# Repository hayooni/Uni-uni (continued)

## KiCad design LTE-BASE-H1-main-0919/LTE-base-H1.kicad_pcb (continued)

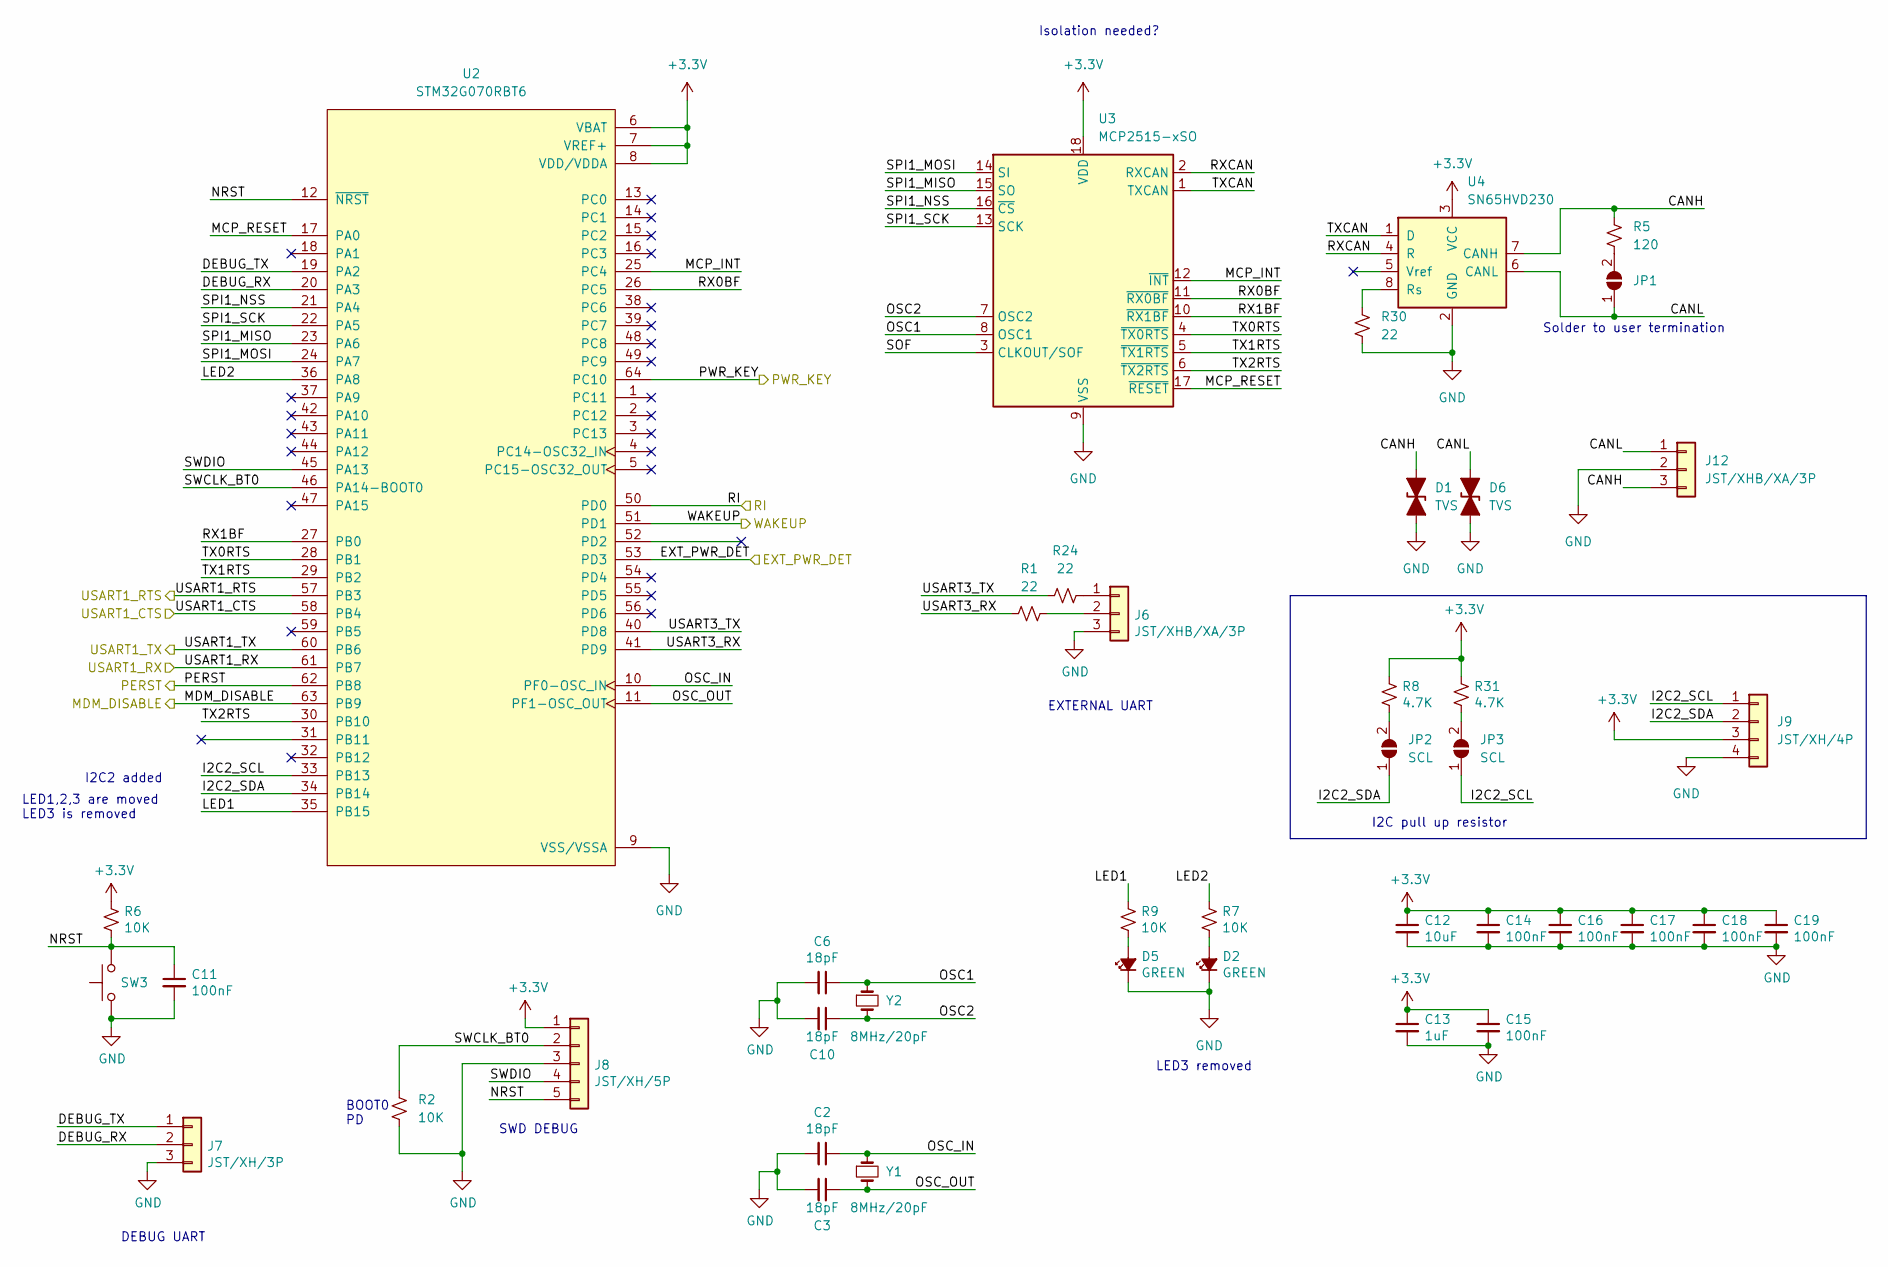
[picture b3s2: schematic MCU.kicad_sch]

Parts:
C2, C3, C6, C10: 18pF; C_0603_1608Metric; LCSC C1647
C11, C14, C15, C16, C17, C18, C19: 100nF; C_0603_1608Metric; LCSC C14663
C12: 10uF; C_0603_1608Metric; LCSC C19702
C13: 1uF; C_0603_1608Metric; LCSC C15849
D1, D6: TVS; D_SOD-323; LCSC C314256
D2, D5: GREEN; LED_0603_1608Metric; LCSC C72043
J6, J12: JST/XHB/XA/3P; JST_XA_S03B-XASK-1N-BN_1x03_P2.50mm_Horizontal; LCSC C95477
J7: JST/XH/3P; JST_XH_B3B-XH-A_1x03_P2.50mm_Vertical; LCSC C144394
J8: JST/XH/5P; JST_XH_B5B-XH-A_1x05_P2.50mm_Vertical; LCSC C157991
J9: JST/XH/4P; JST_XH_B4B-XH-A_1x04_P2.50mm_Vertical
JP1: SolderJumper_2_Open; SolderJumper-2_P1.3mm_Open_RoundedPad1.0x1.5mm
JP2, JP3: SCL; SolderJumper-2_P1.3mm_Open_RoundedPad1.0x1.5mm
R1, R24, R30: 22; R_0603_1608Metric; LCSC C23345
R2, R6, R7, R9: 10K; R_0603_1608Metric; LCSC C25804
R5: 120; R_0603_1608Metric; LCSC C22787
R8, R31: 4.7K; R_0603_1608Metric
SW3: SW_Push; SW_SPST_PTS645; LCSC C2834943
U2: STM32G070RBT6; LQFP-64_10x10mm_P0.5mm; LCSC C529340
U3: MCP2515-xSO; SOIC-18W_7.5x11.6mm_P1.27mm; LCSC C153782
U4: SN65HVD230; SOIC-8_3.9x4.9mm_P1.27mm
Y1, Y2: 8MHz/20pF; Crystal_SMD_5032-2Pin_5.0x3.2mm; LCSC C115962

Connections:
/BG96/DTR: U2.51 (PD1); also elsewhere on the board
/BG96/PWRKEY: U2.64 (PC10); also elsewhere on the board
/BG96/RI: U2.50 (PD0); also elsewhere on the board
/BG96/nPERST: U2.62 (PB8); also elsewhere on the board
/BG96/nW_DISABLE: U2.63 (PB9); also elsewhere on the board
/EXT_PWR_DET: U2.53 (PD3); also elsewhere on the board
/MCU/CANH: D1.2 (A2), J12.3, R5.1, U4.7 (CANH)
/MCU/CANL: D6.2 (A2), J12.1, JP1.1 (A), U4.6 (CANL)
/MCU/DEBUG_RX: J7.2, U2.20 (PA3)
/MCU/DEBUG_TX: J7.1, U2.19 (PA2)
/MCU/I2C2_SCL: J9.1, JP3.1 (A), U2.33 (PB13)
/MCU/I2C2_SDA: J9.2, JP2.1 (A), U2.34 (PB14)
/MCU/LED1: R9.1, U2.35 (PB15)
/MCU/LED2: R7.1, U2.36 (PA8)
/MCU/MCP_INT: U2.25 (PC4), U3.12 (~INT)
/MCU/MCP_RESET: U2.17 (PA0), U3.17 (~RESET)
/MCU/NRST: C11.1, J8.5, R6.2, SW3.1, U2.12 (~NRST)
/MCU/OSC1: C6.1, U3.8 (OSC1), Y2.1
/MCU/OSC2: C10.1, U3.7 (OSC2), Y2.2
/MCU/OSC_IN: C2.1, U2.10 (PF0-OSC_IN), Y1.1
/MCU/OSC_OUT: C3.1, U2.11 (PF1-OSC_OUT), Y1.2
/MCU/RX0BF: U2.26 (PC5), U3.11 (~RX0BF)
/MCU/RX1BF: U2.27 (PB0), U3.10 (~RX1BF)
/MCU/RXCAN: U3.2 (RXCAN), U4.4 (R)
/MCU/SOF: U3.3 (CLKOUT/SOF)
/MCU/SPI1_MISO: U2.23 (PA6), U3.15 (SO)
/MCU/SPI1_MOSI: U2.24 (PA7), U3.14 (SI)
/MCU/SPI1_NSS: U2.21 (PA4), U3.16 (~CS)
/MCU/SPI1_SCK: U2.22 (PA5), U3.13 (SCK)
/MCU/SWCLK_BT0: J8.2, R2.1, U2.46 (PA14-BOOT0)
/MCU/SWDIO: J8.4, U2.45 (PA13)
/MCU/TX0RTS: U2.28 (PB1), U3.4 (~TX0RTS)
/MCU/TX1RTS: U2.29 (PB2), U3.5 (~TX1RTS)
/MCU/TX2RTS: U2.30 (PB10), U3.6 (~TX2RTS)
/MCU/TXCAN: U3.1 (TXCAN), U4.1 (D)
/MCU/USART1_CTS: U2.58 (PB4); also elsewhere on the board
/MCU/USART1_RTS: U2.57 (PB3); also elsewhere on the board
/MCU/USART1_RX: U2.61 (PB7); also elsewhere on the board
/MCU/USART1_TX: U2.60 (PB6); also elsewhere on the board
/MCU/USART3_RX: R1.1, U2.41 (PD9)
/MCU/USART3_TX: R24.1, U2.40 (PD8)
GND: C2.2, C3.2, C6.2, C10.2, C11.2, C12.2, C13.2, C14.2, C15.2, C16.2, C17.2, C18.2, C19.2, D1.1 (A1), D2.1 (K), D5.1 (K), D6.1 (A1), J6.3, J7.3, J8.3, J9.4, J12.2, R2.2, R30.1, SW3.2, U2.9 (VSS/VSSA), U3.9 (VSS), U4.2 (GND); also elsewhere on the board
unnamed: D2.2 (A), R7.2
unnamed: D5.2 (A), R9.2
unnamed: J6.1, R24.2
unnamed: J6.2, R1.2
unnamed: JP1.2 (B), R5.2
unnamed: JP2.2 (B), R8.2
unnamed: JP3.2 (B), R31.2
unnamed: R30.2, U4.8 (Rs)

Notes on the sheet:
LED1,2,3 are moved LED3 is removed
LED3 removed
BOOT0 PD
SWD DEBUG
I2C pull up resistor
Isolation needed?
I2C2 added
Solder to user termination
EXTERNAL UART
DEBUG UART

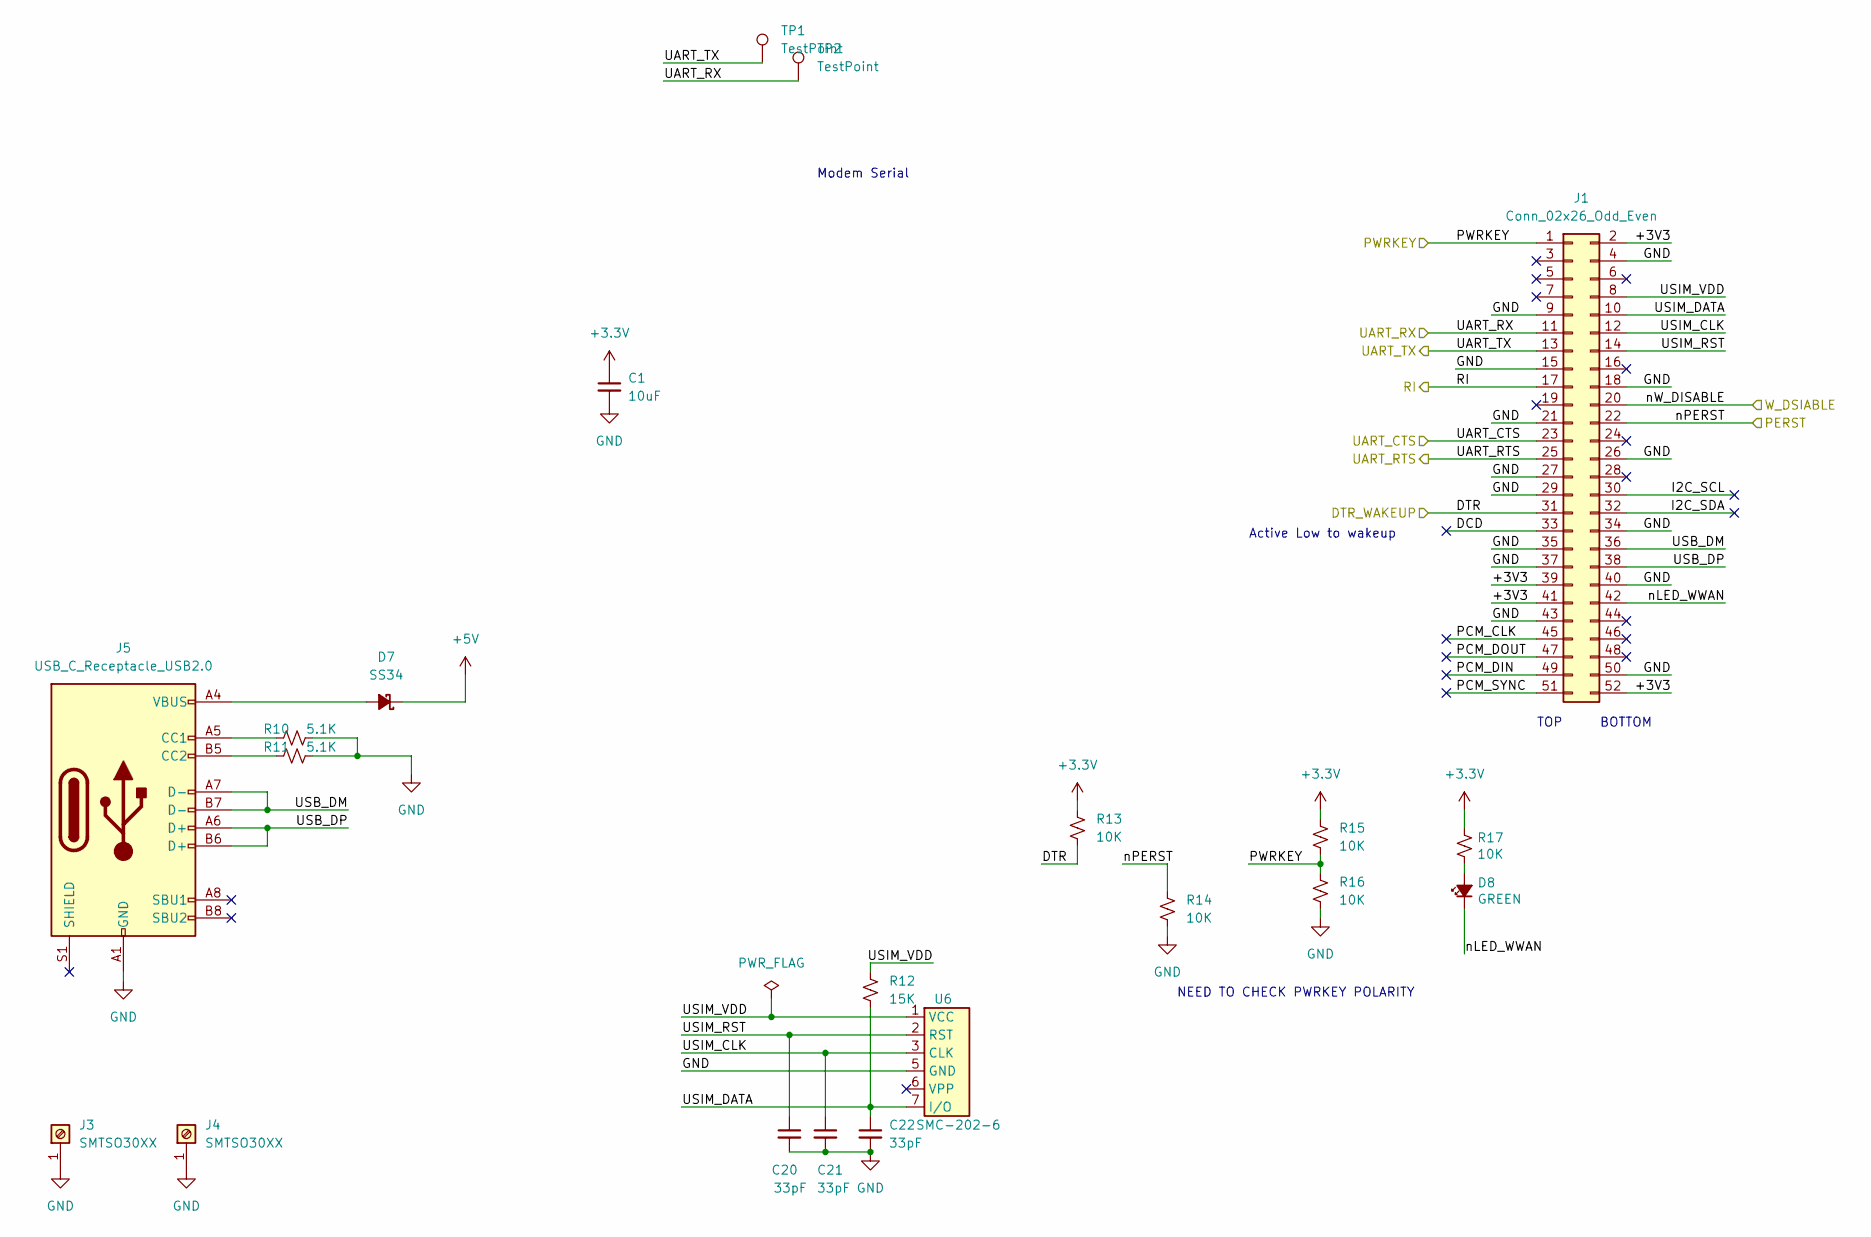
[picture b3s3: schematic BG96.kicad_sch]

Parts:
C1: 10uF; C_0603_1608Metric; LCSC C19702
C20, C21, C22: 33pF; C_0603_1608Metric_Pad1.08x0.95mm_HandSolder; LCSC C1663
D7: SS34; D_SMA; LCSC C8678
D8: GREEN; LED_0603_1608Metric; LCSC C72043
J1: Conn_02x26_Odd_Even; BUS_PCI_Express_Mini_Full; LCSC C444928
J3, J4: SMTSO30XX
J5: USB_C_Receptacle_USB2.0; USB_C_Receptacle_HRO_TYPE-C-31-M-12; LCSC C165948
R10, R11: 5.1K; R_0805_2012Metric; LCSC C27834
R12: 15K; R_0603_1608Metric_Pad0.98x0.95mm_HandSolder; LCSC C22809
R13, R14, R15, R16: 10K; R_0603_1608Metric_Pad0.98x0.95mm_HandSolder; LCSC C25804
R17: 10K; R_0603_1608Metric; LCSC C25804
TP1, TP2: TestPoint; TestPoint_Keystone_5000-5004_Miniature
U6: SMC-202-6; LCSC C266634

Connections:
+5V: D7.1 (K); also elsewhere on the board
/BG96/DCD: J1.33
/BG96/DTR: J1.31, R13.2; also elsewhere on the board
/BG96/I2C_SCL: J1.30
/BG96/I2C_SDA: J1.32
/BG96/PCM_CLK: J1.45
/BG96/PCM_DIN: J1.49
/BG96/PCM_DOUT: J1.47
/BG96/PCM_SYNC: J1.51
/BG96/PWRKEY: J1.1, R15.2, R16.1; also elsewhere on the board
/BG96/RI: J1.17; also elsewhere on the board
/BG96/UART_CTS: J1.23; also elsewhere on the board
/BG96/UART_RTS: J1.25; also elsewhere on the board
/BG96/UART_RX: J1.11, TP2.1; also elsewhere on the board
/BG96/UART_TX: J1.13, TP1.1; also elsewhere on the board
/BG96/USB_DM: J1.36, J5.A7 (D-), J5.B7 (D-)
/BG96/USB_DP: J1.38, J5.A6 (D+), J5.B6 (D+)
/BG96/USIM_CLK: C21.1, J1.12, U6.3 (CLK)
/BG96/USIM_DATA: C22.1, J1.10, R12.2, U6.7 (I/O)
/BG96/USIM_RST: C20.1, J1.14, U6.2 (RST)
/BG96/USIM_VDD: J1.8, R12.1, U6.1 (VCC)
/BG96/nLED_WWAN: D8.1 (K), J1.42
/BG96/nPERST: J1.22, R14.1; also elsewhere on the board
/BG96/nW_DISABLE: J1.20; also elsewhere on the board
GND: C1.2, C20.2, C21.2, C22.2, J1.4, J1.9, J1.15, J1.18, J1.21, J1.26, J1.27, J1.29, J1.34, J1.35, J1.37, J1.40, J1.43, J1.50, J3.1, J4.1, J5.A1 (GND), J5.A12 (GND), J5.B1 (GND), J5.B12 (GND), R10.1, R11.1, R14.2, R16.2, U6.5 (GND); also elsewhere on the board
unnamed: D7.2 (A), J5.A4 (VBUS), J5.A9 (VBUS), J5.B4 (VBUS), J5.B9 (VBUS)
unnamed: D8.2 (A), R17.2
unnamed: J5.A5 (CC1), R10.2
unnamed: J5.B5 (CC2), R11.2

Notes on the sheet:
Modem Serial
BOTTOM
Active Low to wakeup
TOP
NEED TO CHECK PWRKEY POLARITY

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
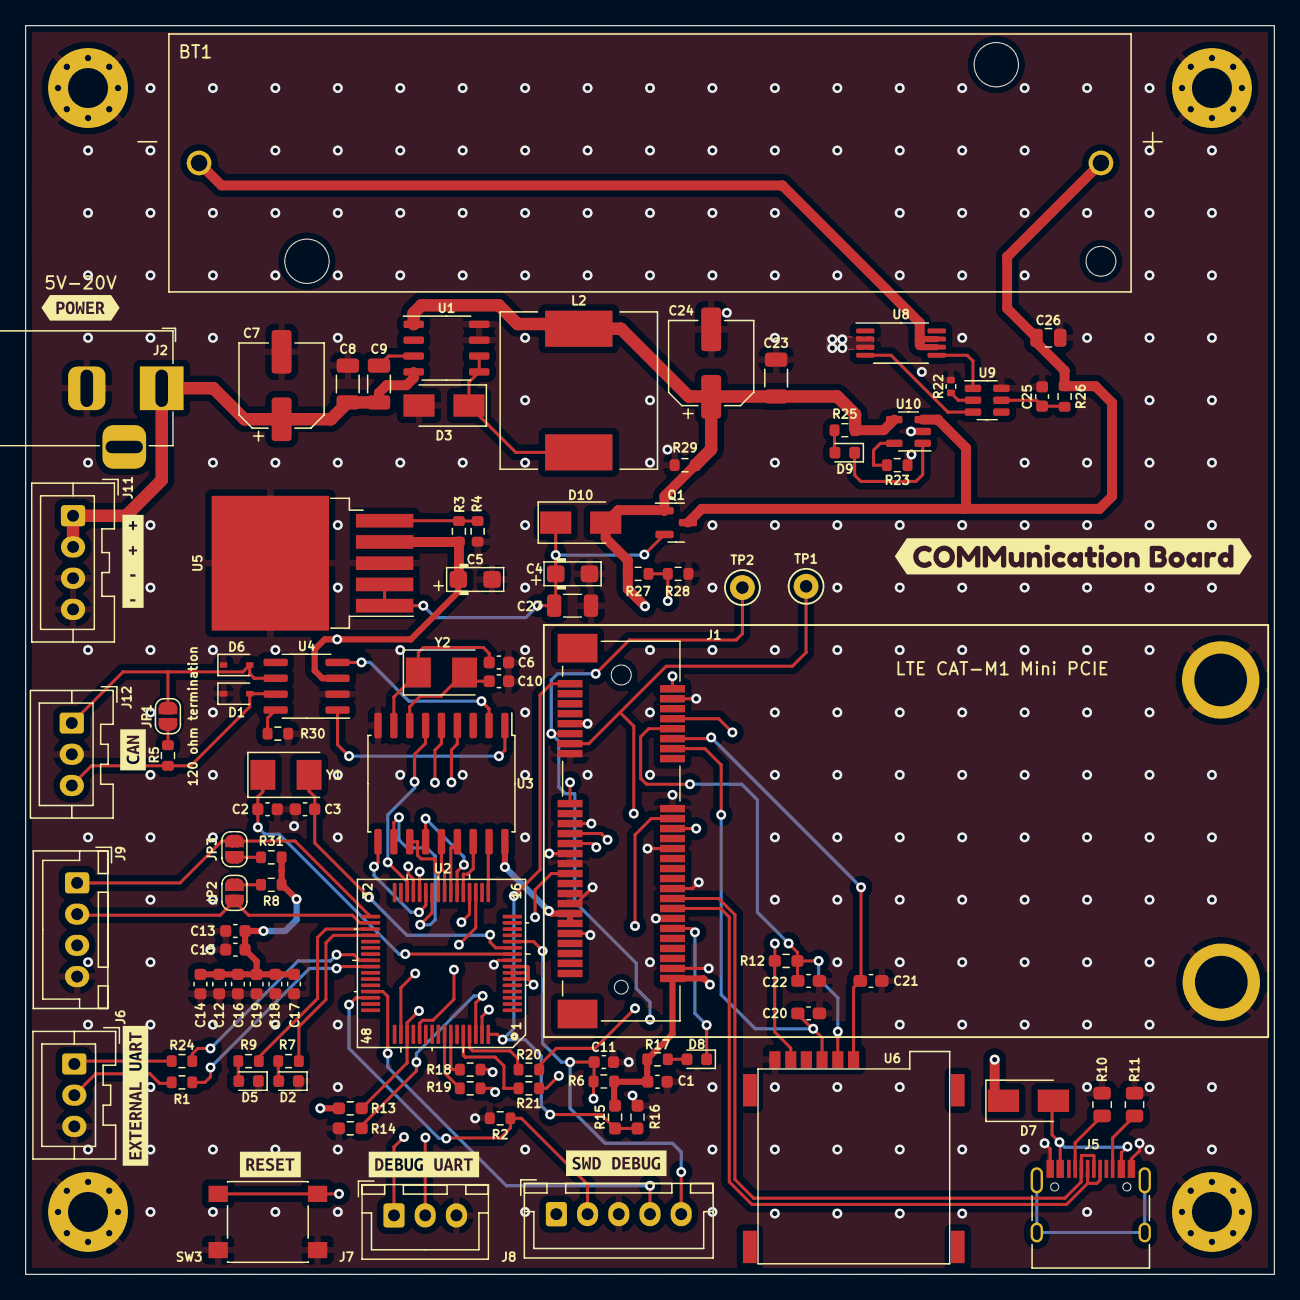
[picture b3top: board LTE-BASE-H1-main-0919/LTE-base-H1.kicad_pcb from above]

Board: 4 copper layers, 100.0 x 100.0 mm, 110 parts (0 on the bottom side), 80 nets.

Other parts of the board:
kibuzzard-61FFCA2F: G***; kibuzzard-61FFCA2F
kibuzzard-61FFCA5B: G***; kibuzzard-61FFCA5B
kibuzzard-61FFCA89: G***; kibuzzard-61FFCA89
kibuzzard-61FFCAE2: G***; kibuzzard-61FFCAE2
kibuzzard-61FFCAF5: G***; kibuzzard-61FFCAF5
kibuzzard-61FFCBAB: G***; kibuzzard-61FFCBAB
kibuzzard-61FFCBC3: G***; kibuzzard-61FFCBC3
kibuzzard-6200D0E6: G***; kibuzzard-6200D0E6

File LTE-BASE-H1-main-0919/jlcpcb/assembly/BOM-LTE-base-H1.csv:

Comment,Designator,Footprint,LCSC
DMG2307L,Q1,SOT-23,C102620
8MHz/20pF,"Y1,Y2",Crystal_SMD_5032-2Pin_5.0x3.2mm,C115962
1K,R22,R_0402_1005Metric,C11702
SN65HVD230,U4,SOIC-8_3.9x4.9mm_P1.27mm,C12084
Barrel Jack,J2,BarrelJack_Horizontal,C136744
DW01A,U9,SOT-23-6,C14213
JST/XHB/XA/3P,"J12,J6,J7",JST_XA_B03B-XASK-1_1x03_P2.50mm_Vertical,C144394
JST/XHB/XA/4P,"J11,J9",JST_XA_B04B-XASK-1_1x04_P2.50mm_Vertical,C144395
100nF,"C11,C14,C15,C16,C17,C18,C19,C25",C_0603_1608Metric,C14663
MCP73831-2-OT,U10,SOT-23-5,C14879
MCP2515-xSO,U3,SOIC-18W_7.5x11.6mm_P1.27mm,C153782
JST/XH/5P,J8,JST_XH_B5B-XH-A_1x05_P2.50mm_Vertical,C157991
1uF,C13,C_0603_1608Metric,C15849
FS8205A,U8,TSSOP-8_4.4x3mm_P0.65mm,C16052
18pF,"C10,C2,C3,C6",C_0603_1608Metric,C1647
USB_C_Receptacle_USB2.0,J5,USB_C_Receptacle_HRO_TYPE-C-31-M-12,C165948
33pF,"C20,C21,C22",C_0603_1608Metric_Pad1.08x0.95mm_HandSolder,C1663
4.7uF,C26,C_0805_2012Metric,C1779
1uF,"C23,C27,C8,C9",C_1206_3216Metric,C1848
10uF,"C1,C12",C_0603_1608Metric,C19702
1K,R25,R_0603_1608Metric,C21190
100,R26,R_0603_1608Metric,C22775
120,R5,R_0603_1608Metric,C22787
15K,R12,R_0603_1608Metric_Pad0.98x0.95mm_HandSolder,C22809
10.69K,R3,R_0603_1608Metric,C22857
RED,D9,LED_0603_1608Metric,C2286
2K,R23,R_0603_1608Metric,C22975
4.7K,"R31,R8",R_0603_1608Metric,C23162
22,"R1,R18,R19,R20,R21,R24,R30",R_0603_1608Metric,C23345
10K,"R13,R14,R15,R16,R17,R2,R27,R29,R4,R6,R7,R9",R_0603_1608Metric_Pad0.98x0.95mm_HandSolder,C25804
SMC-202-6,U6,SMC-202-6,C266634
5.1K,"R10,R11",R_0805_2012Metric,C27834
SW_Push,SW3,SW_SPST_PTS645,C2834943
TVS,"D1,D6",D_SOD-323,C314256
20K,R28,R_0603_1608Metric,C4184
Conn_02x26_Odd_Even,J1,BUS_PCI_Express_Mini_Full,C444928
47uF,"C24,C7",CP_Elec_6.3x5.8,C445227
STM32G070RBT6,U2,LQFP-64_10x10mm_P0.5mm,C529340
10uF,"C4,C5",CP_EIA-3216-18_Kemet-A,C7171
GREEN,"D2,D5,D8",LED_0603_1608Metric,C72043
XL2012,U1,SOP-8_3.9x4.9mm_P1.27mm,C73338
SS34,"D10,D3,D7",D_SMA,C8678
MIC29302WU,U5,TO-263-5_TabPin3,C9013
47uH/3A,L2,L_12x12mm_H8mm,C9906
MountingHole_Pad,H4,MountingHole_3.2mm_M3_Pad_Via,
SMTSO30XX,J4,SMTSO30XX,
MountingHole_Pad,H2,MountingHole_3.2mm_M3_Pad_Via,
SMTSO30XX,J3,SMTSO30XX,
MountingHole_Pad,H1,MountingHole_3.2mm_M3_Pad_Via,
SolderJumper_2_Open,JP1,SolderJumper-2_P1.3mm_Open_RoundedPad1.0x1.5mm,
MountingHole_Pad,H3,MountingHole_3.2mm_M3_Pad_Via,
TestPoint,TP2,TestPoint_Keystone_5000-5004_Miniature,
TestPoint,TP1,TestPoint_Keystone_5000-5004_Miniature,
Batt holder,BT1,BAT_1043,
SCL,JP3,SolderJumper-2_P1.3mm_Open_RoundedPad1.0x1.5mm,
SCL,JP2,SolderJumper-2_P1.3mm_Open_RoundedPad1.0x1.5mm,

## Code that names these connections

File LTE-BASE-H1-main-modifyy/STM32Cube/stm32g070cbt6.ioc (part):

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Mcu.Name=STM32G070RBTx
Mcu.Package=LQFP64
Mcu.UserName=STM32G070RBTx
PA13.Mode=Serial_Wire
PA13.Signal=SYS_SWDIO
PA14-BOOT0.Mode=Serial_Wire
PA14-BOOT0.Signal=SYS_SWCLK
PA2.Mode=Asynchronous
PA2.Signal=USART2_TX
PA3.Mode=Asynchronous
PA3.Signal=USART2_RX
PA4.Mode=NSS_Signal_Hard_Output
PA4.Signal=SPI1_NSS
PA5.Mode=Full_Duplex_Master
PA5.Signal=SPI1_SCK
PA6.Mode=Full_Duplex_Master
PA6.Signal=SPI1_MISO
PA7.Mode=Full_Duplex_Master
PA7.Signal=SPI1_MOSI
PA8.Signal=GPIO_Output
PB13.Mode=I2C
PB13.Signal=I2C2_SCL
PB14.Mode=I2C
PB14.Signal=I2C2_SDA
PB15.Signal=GPIO_Output
PB3.Mode=CTS_RTS
PB3.Signal=USART1_RTS
PB4.Mode=CTS_RTS
PB4.Signal=USART1_CTS
PB6.Mode=Asynchronous
PB6.Signal=USART1_TX
PB7.Mode=Asynchronous
PB7.Signal=USART1_RX
PC1.Signal=GPIO_Output
PC14-OSC32_IN\ (PC14).Mode=LSE-External-Oscillator
PC14-OSC32_IN\ (PC14).Signal=RCC_OSC32_IN
PC15-OSC32_OUT\ (PC15).Mode=LSE-External-Oscillator
PC15-OSC32_OUT\ (PC15).Signal=RCC_OSC32_OUT
PD8.Mode=Asynchronous
PD8.Signal=USART3_TX
PD9.Mode=Asynchronous
PD9.Signal=USART3_RX
PF0-OSC_IN\ (PF0).Mode=HSE-External-Oscillator
PF0-OSC_IN\ (PF0).Signal=RCC_OSC_IN
PF1-OSC_OUT\ (PF1).Mode=HSE-External-Oscillator
PF1-OSC_OUT\ (PF1).Signal=RCC_OSC_OUT
RCC.HSE_VALUE=8000000
RCC.SYSCLKFreq_VALUE=16000000
board=custom

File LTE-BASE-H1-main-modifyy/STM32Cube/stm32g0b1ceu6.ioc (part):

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Mcu.Name=STM32G0B1C(B-C-E)Ux
Mcu.Package=UFQFPN48
Mcu.UserName=STM32G0B1CEUx
PA1.Mode=IN1
PA1.Signal=ADC1_IN1
PA11\ [PA9].Mode=FDCAN_Activate
PA11\ [PA9].Signal=FDCAN1_RX
PA12\ [PA10].Mode=FDCAN_Activate
PA12\ [PA10].Signal=FDCAN1_TX
PA13.Mode=Serial_Wire
PA13.Signal=SYS_SWDIO
PA14-BOOT0.Mode=Serial_Wire
PA14-BOOT0.Signal=SYS_SWCLK
PA2.Mode=Asynchronous
PA2.Signal=USART2_TX
PA3.Mode=Asynchronous
PA3.Signal=USART2_RX
PB1.Mode=RTS_Only
PB1.Signal=USART3_RTS
PB10.Mode=Asynchronous
PB10.Signal=USART3_TX
PB11.Mode=Asynchronous
PB11.Signal=USART3_RX
PB13.Mode=I2C
PB13.Signal=I2C2_SCL
PB14.Mode=I2C
PB14.Signal=I2C2_SDA
PB15.Signal=GPIO_Input
PB3.Mode=CTS_RTS
PB3.Signal=USART1_RTS
PB4.Mode=CTS_RTS
PB4.Signal=USART1_CTS
PB5.Mode=SYS_WakeUp6
PB5.Signal=SYS_WKUP6
PB6.Mode=Asynchronous
PB6.Signal=USART1_TX
PB7.Mode=Asynchronous
PB7.Signal=USART1_RX
PC14-OSC32_IN\ (PC14).Mode=LSE-External-Oscillator
PC14-OSC32_IN\ (PC14).Signal=RCC_OSC32_IN
PC15-OSC32_OUT\ (PC15).Mode=LSE-External-Oscillator
PC15-OSC32_OUT\ (PC15).Signal=RCC_OSC32_OUT
PD2.Signal=GPIO_Output
PD3.Signal=GPIO_Input
PF0-OSC_IN\ (PF0).Mode=HSE-External-Oscillator
PF0-OSC_IN\ (PF0).Signal=RCC_OSC_IN
PF1-OSC_OUT\ (PF1).Mode=HSE-External-Oscillator
PF1-OSC_OUT\ (PF1).Signal=RCC_OSC_OUT
PF2-NRST.Signal=GPIO_Input
RCC.HSE_VALUE=8000000
RCC.SYSCLKFreq_VALUE=16000000
board=custom

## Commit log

2022-10-18 C++ 세미나
2022-10-20 lte보드 올리기 테스트
2022-11-25 아트웍 진행중
